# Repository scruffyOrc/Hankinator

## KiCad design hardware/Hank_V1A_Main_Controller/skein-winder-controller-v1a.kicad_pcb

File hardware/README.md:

# Hank hardware sources

This directory contains the editable KiCad sources and the corresponding
released manufacturing artifacts for the hardware used by Hank Winder V1.

| Directory | Board | Release source |
| --- | --- | --- |
| `Hank_V1A_Main_Controller` | Hank V1A main controller | V1A released controller package |
| `Load_Cell_System` | HX711 breakout and front/rear smart-foot load-cell boards | Load-cell-system release package |
| `Distribution_Block_v1.1` | Load-cell distribution block | v1.1 confirmed JLC release |
| `Hall_Effect_Board_A2` | Hall-effect sensor board | A2 release package |
| `Hank_Touchscreen_Adapter` | V1A-to-touchscreen adapter | Rev A two-layer package |

KiCad local state files (`*.kicad_prl`), lock files, and local `.history`
directories are intentionally excluded. They are machine-specific and are not
authoritative design data.

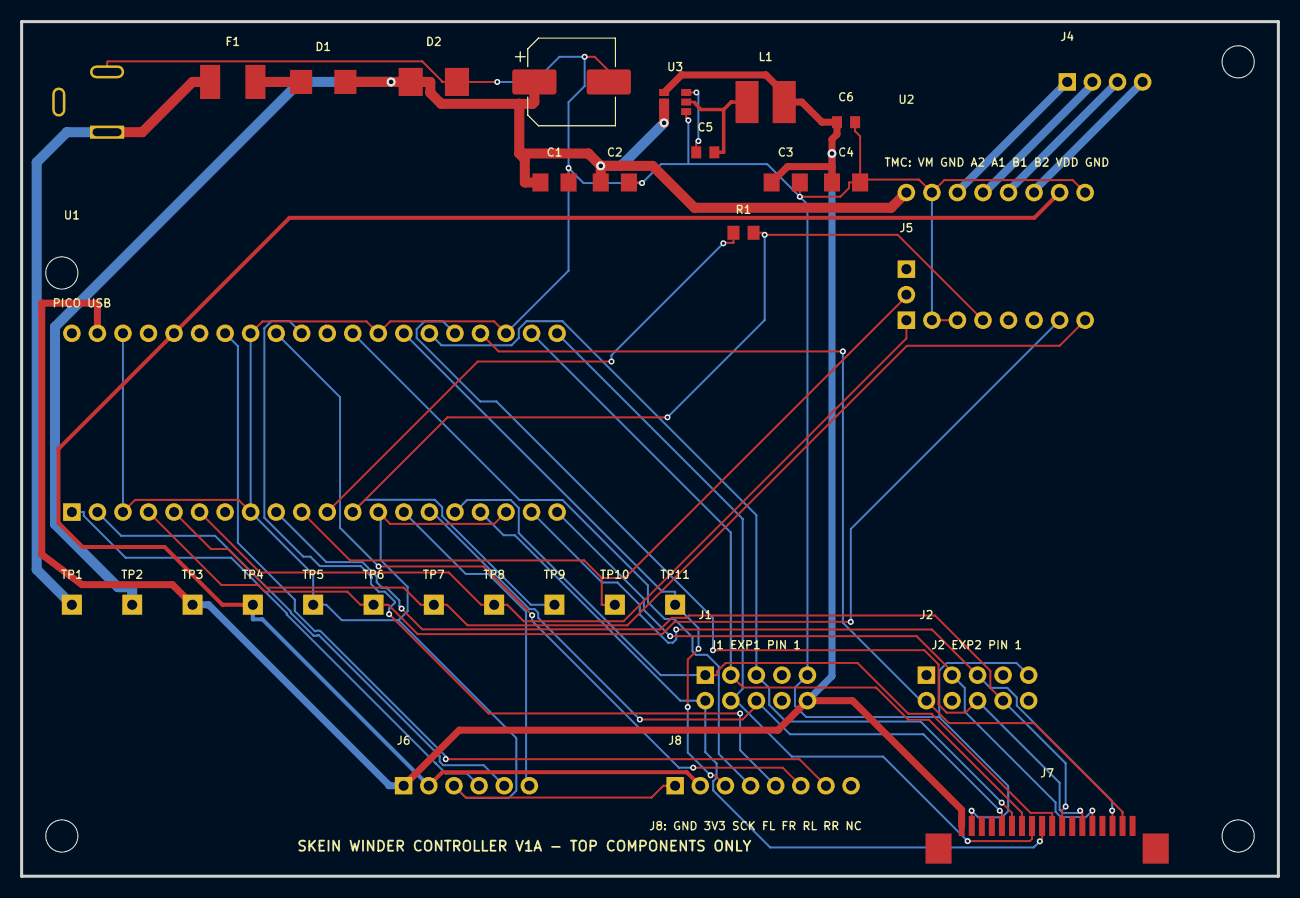
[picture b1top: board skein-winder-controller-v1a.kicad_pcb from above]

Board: 2 copper layers, 125.0 x 85.0 mm, 38 parts (0 on the bottom side), 37 nets.

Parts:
C1: 10uF 35V; C1
C2: 10uF 35V; C2
C3: 22uF 10V; C3
C4: 22uF 10V; C4
C5: 100nF bootstrap; C5
C6: 100nF 5V; C6
C7: CP_Elec_8x10.5
D1: SS54 series reverse-polarity diode; D1
D2: SMBJ18A TVS; D2
F1: PTC 1.1A 1812; F1
H1: M3 NPTH; H1
H2: M3 NPTH; H2
H3: M3 NPTH; H3
H4: M3 NPTH; H4
J1: Mini12864 J1 keyed 2x5 cable header; J1
J2: Mini12864 J2 keyed 2x5 cable header; J2
J3: Measured 5.5x2.1 center-positive blade DC jack; J3
J4: Motor A2 A1 B1 B2; J4
J5: BTT TMC2209 VREF/DIAG 1x2 female socket; J5
J6: Expansion 5V 3V3 GND GP0 GP1 GP10; J6
J7: Mini12864 V2 FPC AFA07-S18FCC-00 C23826; J7
J8: HX711 smart-foot harness GND 3V3 SCK FL FR RL RR 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; J8
L1: 4.7uH 3A; L1
R1: 1k TMC UART TX resistor 0805; R1
TP1: 12V_RAW test point; TP1
TP2: 12V_PROT test point; TP2
TP3: 5V test point; TP3
TP4: 3V3 test point; TP4
TP5: GND test point; TP5
TP6: STEP test point; TP6
TP7: DIR test point; TP7
TP8: EN test point; TP8
TP9: TMC_UART test point; TP9
TP10: TMC_DIAG test point; TP10
TP11: HX_SCK test point; TP11
U1: Raspberry Pi Pico-family 40-pin socket; USB LEFT; U1
U2: BTT TMC2209 V1.2 socket; U2
U3: AP63205WU-7 fixed 5V; U3

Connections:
3V3: J6.2, J8.2, TP4.1, U1.36, U2.15
5V: C3.1, C4.1, C6.1, J1.10, J6.1, J7.1, L1.2, TP3.1, U1.39, U3.1
12V_FUSED: D1.2, F1.2
12V_PROT: C1.1, C2.1, C7.1, D1.1, D2.1, TP2.1, U2.9, U3.2, U3.3
12V_RAW: F1.1, J3.1, TP1.1
A1: J4.2, U2.12
A2: J4.1, U2.11
B1: J4.3, U2.13
B2: J4.4, U2.14
BEEP: J1.1, J7.10, U1.16
BST: C5.1, U3.6
DIR: TP7.1, U1.5, U2.8
EN: TP8.1, U1.6, U2.1
ENC_A: J2.5, J7.16, U1.19
ENC_B: J2.3, J7.14, U1.20
ENC_BTN: J1.2, J7.9, U1.17
GND: C1.2, C2.2, C3.2, C4.2, C6.2, C7.2, D2.2, J1.9, J2.9, J3.2, J6.3, J7.2, J8.1, TP5.1, U1.3, U1.8, U1.13, U1.18, U1.23, U1.28, U1.33, U1.38, U2.2, U2.3, U2.10, U2.16, U3.4
GP0: J6.4, U1.1
GP1: J6.5, U1.2
GP10: J6.6, U1.14
HX_FL: J8.4, U1.29
HX_FR: J8.5, U1.31
HX_RL: J8.6, U1.32
HX_RR: J8.7, U1.34
HX_SCK: J8.3, TP11.1, U1.27
LCD_CLK: J2.2, J7.17, U1.24
LCD_CS: J1.3, J7.7, U1.22
LCD_MOSI: J2.6, J7.13, U1.25
LCD_RS: J1.4, J7.8, U1.21
LCD_RST: J1.5, J7.6, U1.26
RGB: J1.6, J7.5, U1.15
STEP: TP6.1, U1.4, U2.7
STOP: J2.8, J7.11, U1.9
SW: C5.2, L1.1, U3.5
TMC_DIAG: J5.2, TP10.1, U1.10
TMC_UART: R1.2, TP9.1, U1.12, U2.4
TMC_UART_TX: R1.1, U1.11

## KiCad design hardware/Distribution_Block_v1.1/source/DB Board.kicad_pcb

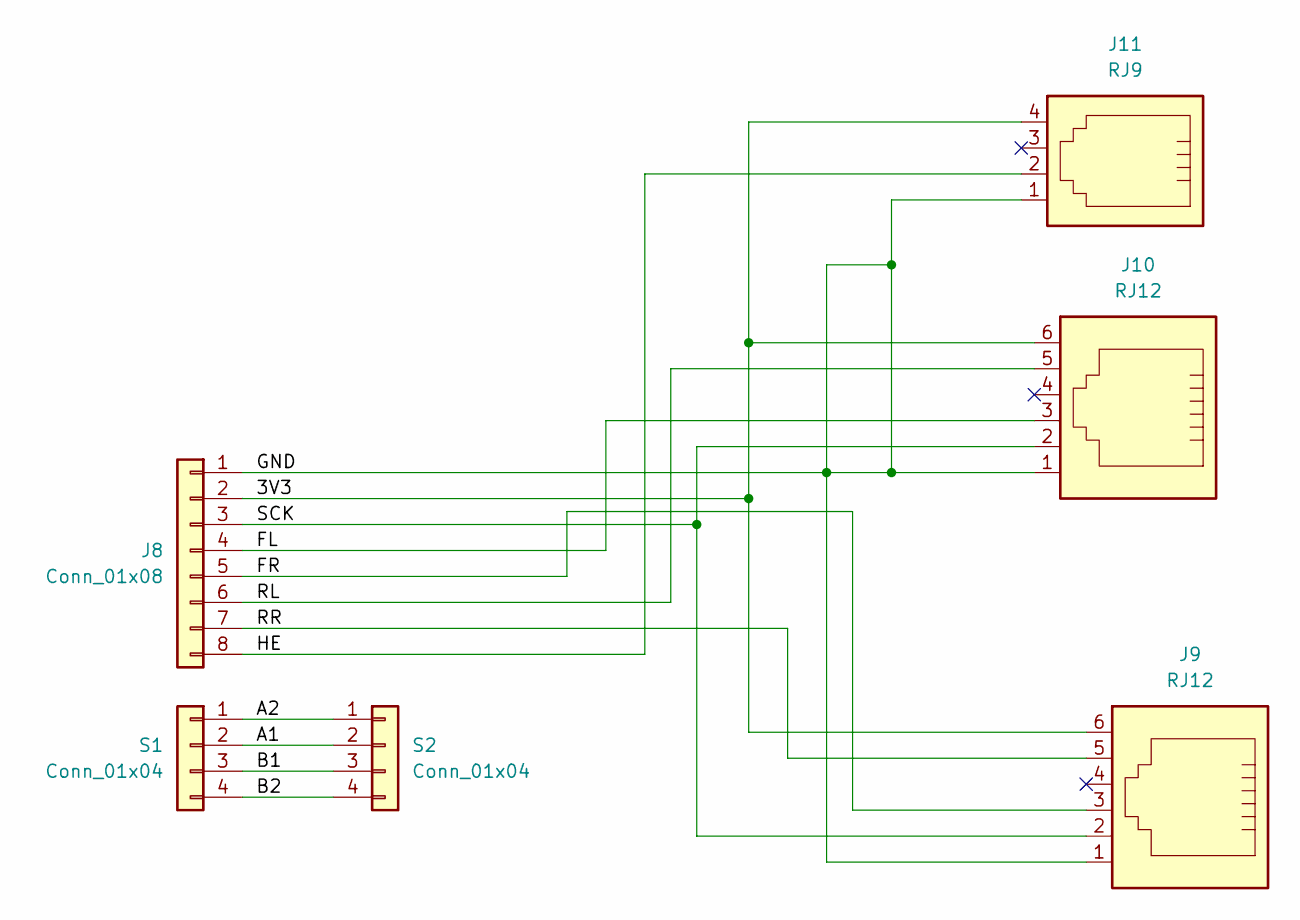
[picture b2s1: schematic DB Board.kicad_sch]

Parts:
J8: Conn_01x08; JST_XH_B8B-XH-A_1x08_P2.50mm_Vertical
J9, J10: RJ12; RJ25_Wayconn_MJEA-660X1_Horizontal
J11: RJ9; RJ9_Evercom_5501-4P4C-13MM_Horizontal
S1, S2: Conn_01x04; JST_XH_B4B-XH-A_1x04_P2.50mm_Vertical

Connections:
/3V3: J8.2, J9.6, J10.6, J11.4
/A1: S1.2, S2.2
/A2: S1.1, S2.1
/B1: S1.3, S2.3
/B2: S1.4, S2.4
/FL: J8.4, J10.3
/FR: J8.5, J9.3
/GND: J8.1, J9.1, J10.1, J11.1
/HE: J8.8, J11.2
/RL: J8.6, J10.5
/RR: J8.7, J9.5
/SCK: J8.3, J9.2, J10.2

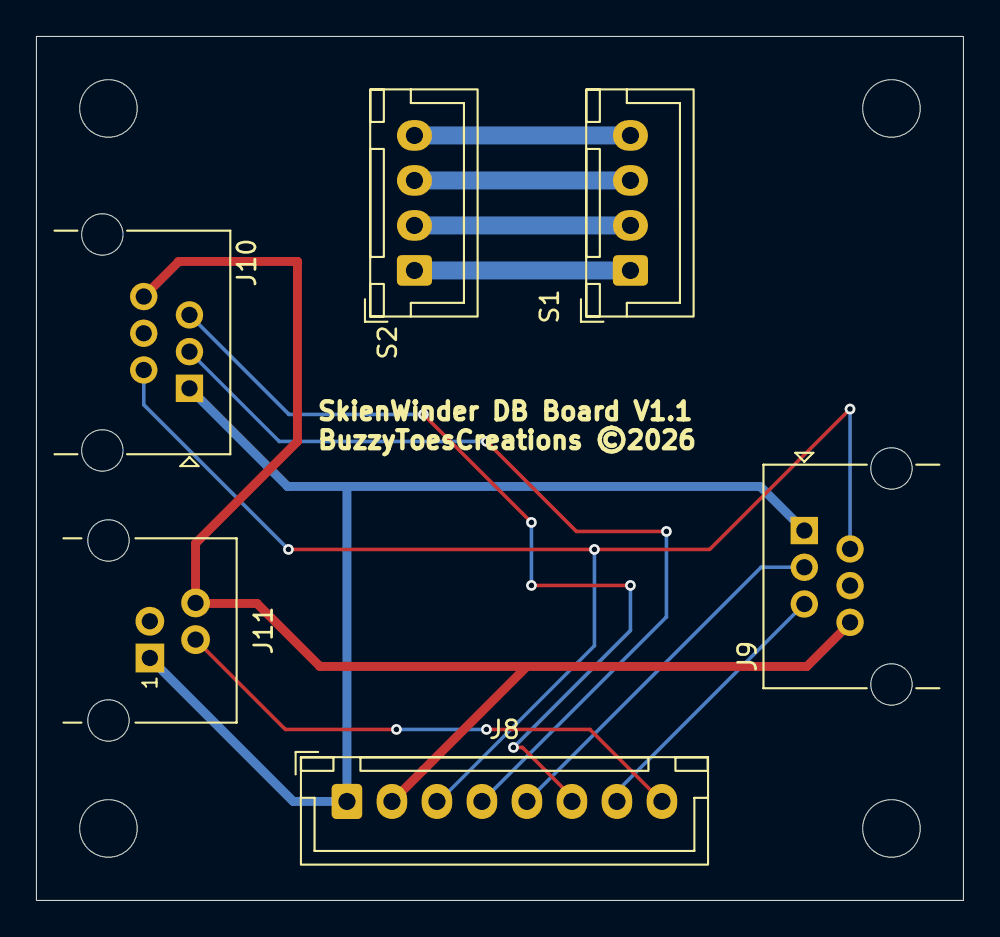
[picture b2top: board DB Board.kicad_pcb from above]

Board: 2 copper layers, 51.5 x 48.0 mm, 10 parts (0 on the bottom side), 12 nets.

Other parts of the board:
H1, H2, H3, H4: MountingHole_3.2mm_M3

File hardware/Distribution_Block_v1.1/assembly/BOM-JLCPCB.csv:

"Comment","Designator","Footprint","LCSC Part #"
"B8B-XH-A(LF)(SN)","J8","JST_XH_B8B-XH-A_1x08_P2.50mm_Vertical","C157972"
"B4B-XH-A(LF)(SN)","S1,S2","JST_XH_B4B-XH-A_1x04_P2.50mm_Vertical","C144395"
"R-RJ11R06P-A801","J9,J10","RJ25_Wayconn_MJEA-660X1_Horizontal","C189747"
"5501-4P4C-13MM","J11","RJ9_Evercom_5501-4P4C-13MM_Horizontal","C3097719"

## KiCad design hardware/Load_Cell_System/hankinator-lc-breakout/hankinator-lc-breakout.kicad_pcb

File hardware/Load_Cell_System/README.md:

# Hankinator load-cell breakout A0

Start with [APPROVAL.html](APPROVAL.html) or [APPROVAL.md](APPROVAL.md). Three editable KiCad 10 projects, preliminary placement only. No Gerbers. See approval report for unresolved sourcing and physical verification gates.

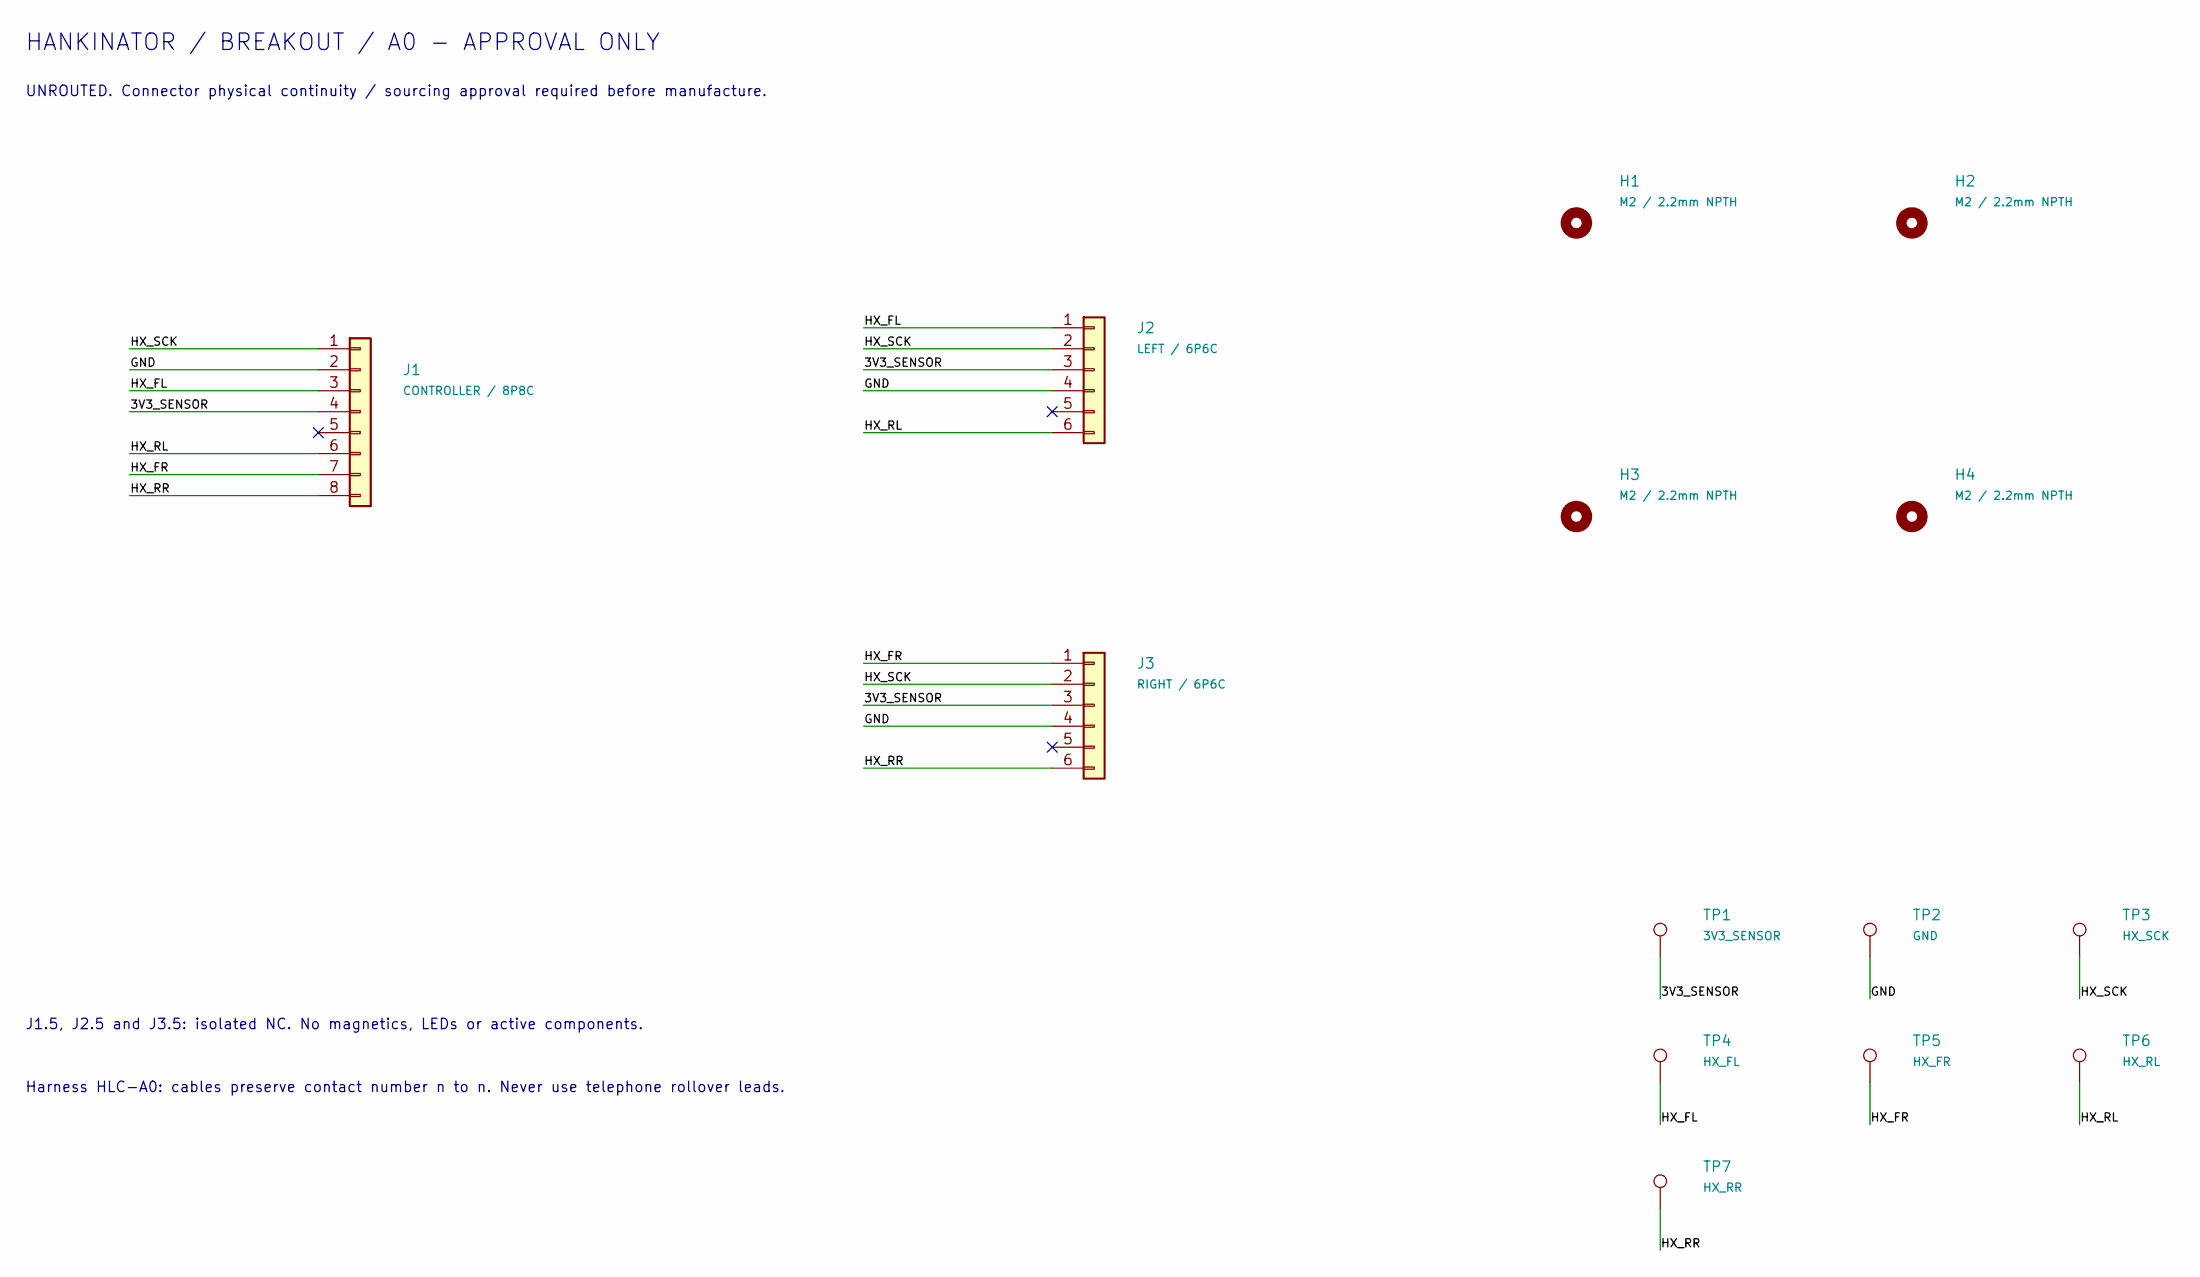
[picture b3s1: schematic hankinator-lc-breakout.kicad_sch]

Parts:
H1, H2, H3, H4: M2 / 2.2mm NPTH; MountingHole_2.2mm_M2
J1: CONTROLLER / 8P8C; WE_615008144221; MPN 615008144221
J2: LEFT / 6P6C; WE_615006143621; MPN 615006143621
J3: RIGHT / 6P6C; WE_615006143621; MPN 615006143621
TP1: 3V3_SENSOR; TestPoint_Pad_D1.5mm
TP2: GND; TestPoint_Pad_D1.5mm
TP3: HX_SCK; TestPoint_Pad_D1.5mm
TP4: HX_FL; TestPoint_Pad_D1.5mm
TP5: HX_FR; TestPoint_Pad_D1.5mm
TP6: HX_RL; TestPoint_Pad_D1.5mm
TP7: HX_RR; TestPoint_Pad_D1.5mm

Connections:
3V3_SENSOR: J1.4, J2.3, J3.3, TP1.1
GND: J1.2, J2.4, J3.4, TP2.1
HX_FL: J1.3, J2.1, TP4.1
HX_FR: J1.7, J3.1, TP5.1
HX_RL: J1.6, J2.6, TP6.1
HX_RR: J1.8, J3.6, TP7.1
HX_SCK: J1.1, J2.2, J3.2, TP3.1

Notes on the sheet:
HANKINATOR / BREAKOUT / A0 - APPROVAL ONLY
UNROUTED. Connector physical continuity / sourcing approval required before manufacture.
J1.5, J2.5 and J3.5: isolated NC. No magnetics, LEDs or active components.
Harness HLC-A0: cables preserve contact number n to n. Never use telephone rollover leads.

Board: 2 copper layers, 14 parts (0 on the bottom side), 7 nets, no tracks yet.

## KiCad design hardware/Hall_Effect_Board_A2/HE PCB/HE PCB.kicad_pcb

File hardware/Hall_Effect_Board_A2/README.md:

# Hankinator HE PCB A2

37 x 20 mm, two copper layers, nominal 1.6 mm FR4 / 1 oz copper. Separate project; DH/RL/FL and controller projects are unchanged.

## A2 changes

Removed 5 mm from the left end. The jack mouth is at CAD X=1, giving approximately 4 mm overhang past the new X=5 board edge. Both 2.3 mm locating holes remain intact; minimum laminate from each hole rim to the left edge is 0.85 mm. Connector mating clearance still needs housing review.

Corrected the sensor footprint from manufacturer bottom view to component-side view, rotated U1 by 180 degrees, and rerouted its supply/output pins. The required flat sensing face points RIGHT. A1's asserted orientation was incorrect; use the A2 Gerbers and CPL together. See POLARITY-REVIEW.md for the complete sensor, LED, MOSFET, and connector review and the required JLC preview orientation.

Added back-side silkscreen: ©Buzzytoes Creations 2026.

## Function

U1 is TI DRV5033AJQLPGM, JLCPCB C201608. Rated 2.5-38 V by the TI datasheet and used here at 3.3 V. It is a continuous digital omnipolar switch, not an analog sensor or a latching switch. Either pole can trigger it. AJ nominal switching thresholds are 6.9 mT operate / 3.5 mT release, with worst-case operate up to 12 mT. Do not assume the same trigger gap as the existing unidentified 3144E module.

D1 PWR and D2 TRIG are red 0603 SMD LEDs, individually labeled. D1 lights with supply. D2 lights while the magnet is detected and goes out when it leaves. It has no pulse stretcher: short detections can be hard to see, and a stationary magnet holds it on.

U1 pulls HALL_N low when detected. R1 is a local 4.7k pull-up to 3.3 V; R2 is 100 ohms in series with the HE cable signal. AO3401A Q1 switches the trigger LED supply, so its LED current does not flow in the sensor output or HE wire. Q1 does add gate capacitance; firmware should measure actual pulse timing if required. C1 is 100 nF near U1; C2 is 10 uF at the input. Each LED has a 1k current-limiting resistor.

## Connector and cable

J1 is the same EVERCOM 5501-4P4C-13MM / C3097719 jack as DH J11. It opens out of the left end. Use a cable verified contact n to contact n; telephone handset cables may reverse contacts.

| Jack contact | DH J11 | Hall J1 |
|---|---|---|
| 1 | GND | GND |
| 2 | HE | HE, active low |
| 3 | Unused | No connect |
| 4 | 3V3 | 3V3_SENSOR |

This is the HALL port mapping, not the smart-foot 4P4C mapping. Connect only to DH J11. The controller Hall allocation remains GP10; verify the installed controller harness actually routes HE there. No firmware or main controller change is included.

## Physical pin check

Component-side PCB coordinates in mm, retaining the A1 CAD origin, X right and Y down. The new outline spans X=5 to 42 and Y=0 to 20; subtract 5 from X to measure from the new left edge:

| J1 contact | X | Y | Function |
|---|---:|---:|---|
| 1, square pad | 9.30 | 11.53 | GND |
| 2 | 11.84 | 10.51 | HE |
| 3 | 9.30 | 9.49 | NC |
| 4 | 11.84 | 8.47 | 3.3 V |

Jack pegs are at (7,5) and (7,15), 2.3 mm NPTH. Signal holes are 0.9 mm. These numbered pad offsets and the 270-degree jack orientation were compared directly against DH J11 and match exactly. The selected manufacturer drawing is included. Do not interpret the staggered solder tails as the plug contact order or mirror this component-side table for fabrication. On the solder side the visual order is reversed. Verify plug contact continuity to the square GND pad and each numbered pad before applying power.

U1 has 1.27 mm pitch and TI's recommended 1.07 x 1.70 mm pads / 0.75 mm drill, from drawing 4221343/C. Pins are 1 VCC, 2 GND, 3 OUT. On this PCB, their coordinates are (40,8.73), (40,10), (40,11.27). The upright flat sensing face points toward the right board edge, as marked MAGNET >. The face is approximately 1.46 mm inside the board edge. Present the magnet toward that face, parallel to the board plane. Mounting height, magnet gap and housing clearance require a prototype check; there is no verified detection-distance claim.

Two 3.2 mm M3 NPTH mounting holes are centered at (18.5,3.5) and (18.5,16.5), 13 mm apart. Use nonmagnetic hardware around the Hall sensor. Leave jack latch and plug withdrawal clearance. The jack is approximately 14.5 mm tall; housing geometry has not been verified.

## Current and traces

All traces are at least 0.20 mm; the short bottom HE connection is 0.25 mm. B.Cu has a continuous ground reference around the short signal route. At 3.3 V, each red LED is approximately 0.9-1.5 mA using the listed 1.8-2.4 V forward range; brightness at these currents must be checked. U1 is 2.7 mA typical, 3.6 mA maximum at 125 C. The active pull-up draws approximately 0.70 mA. The combined conservative operating budget is below 10 mA, excluding external loads on HE.

For a conservative 50 mm long, 0.20 mm wide, 35 um copper trace, resistance is approximately 0.123 ohm at 20 C. At 10 mA this is 1.23 mV drop and 12.3 uW dissipation. These trace widths comfortably support the board's current. Supply drop in the external harness and magnetic switching behavior remain separate checks.

## Files and validation

- `HE PCB/`: editable KiCad schematic, PCB and project; project-local libraries in `libraries/`.
- `HE-PCB-Gerbers.zip`: fabrication layers and separate PTH/NPTH drills.
- `assembly/BOM-JLCPCB.csv` and `assembly/CPL-JLCPCB.csv`: 11 populated components; mounting holes and bare test pads excluded.
- `checks/`: native ERC, native DRC with schematic parity, XML netlist, connector/pad-net audit and assembly inspections.
- `DRILL-COORDINATE-AUDIT.txt`: every exported drill coordinate compared against the PCB.
- `review/`: schematic and board views. Bottom view is shown through the board from the component side, so lettering appears mirrored.

KiCad 10.0.5: ERC 0 errors / 0 warnings; DRC 0 violations / 0 unconnected pads / 0 schematic parity issues under saved project rules. Default ignored check categories are listed in the reports; no individual violations were excluded. CAD checks do not establish physical jack fit, cable continuity, magnet gap, or assembled operation.

## JLCPCB quote / assembly

Upload the Gerber ZIP as a new board item with the BOM and CPL. CPL uses the NEW lower-left board origin at CAD (5,20), millimeters, X right and Y up. Its X coordinates are 5 mm smaller than A1. J1 and U1 coordinates are corrected to their body centers; native KiCad anchor positions are retained in checks/native-positions.csv for comparison. Verify JLC's placement preview: J1 mouth left, U1 flat face right, LED cathodes/pin 1 left. J1 and U1 require through-hole assembly; small-board panel/fixture requirements and costs are determined by JLC.

C201608 has a live JLC listing for wave-solder assembly, but a reliable current stock count was not exposed on the retrieved page. Recheck availability during quoting; do not substitute an unspecified 3144E. Other BOM stock has not been freshly counted for this package. No order has been placed. These files support quoting and first-article fabrication; assembly orientation and actual cable/magnet checks remain required before production use.

## Sources

- TI DRV5033 datasheet: https://www.ti.com/lit/ds/symlink/drv5033.pdf
- JLC sensor listing: https://jlcpcb.com/partdetail/TexasInstruments-DRV5033AJQLPGM/C201608
- AO3401A manufacturer datasheet: https://www.aosmd.com/sites/default/files/res/datasheets/AO3401A.pdf
- JLC Q1 listing: https://jlcpcb.com/partdetail/Alpha_OmegaSemicon-AO3401A/C15127
- JLC LED listing: https://jlcpcb.com/partdetail/Hubei_KentoElec-KT0603R/C2286
- EVERCOM drawing: https://atta.szlcsc.com/upload/public/pdf/source/20220705/442A4794DE2D8659C3975B8A2EE8C1A4.pdf

Prepared 2026-09-30.

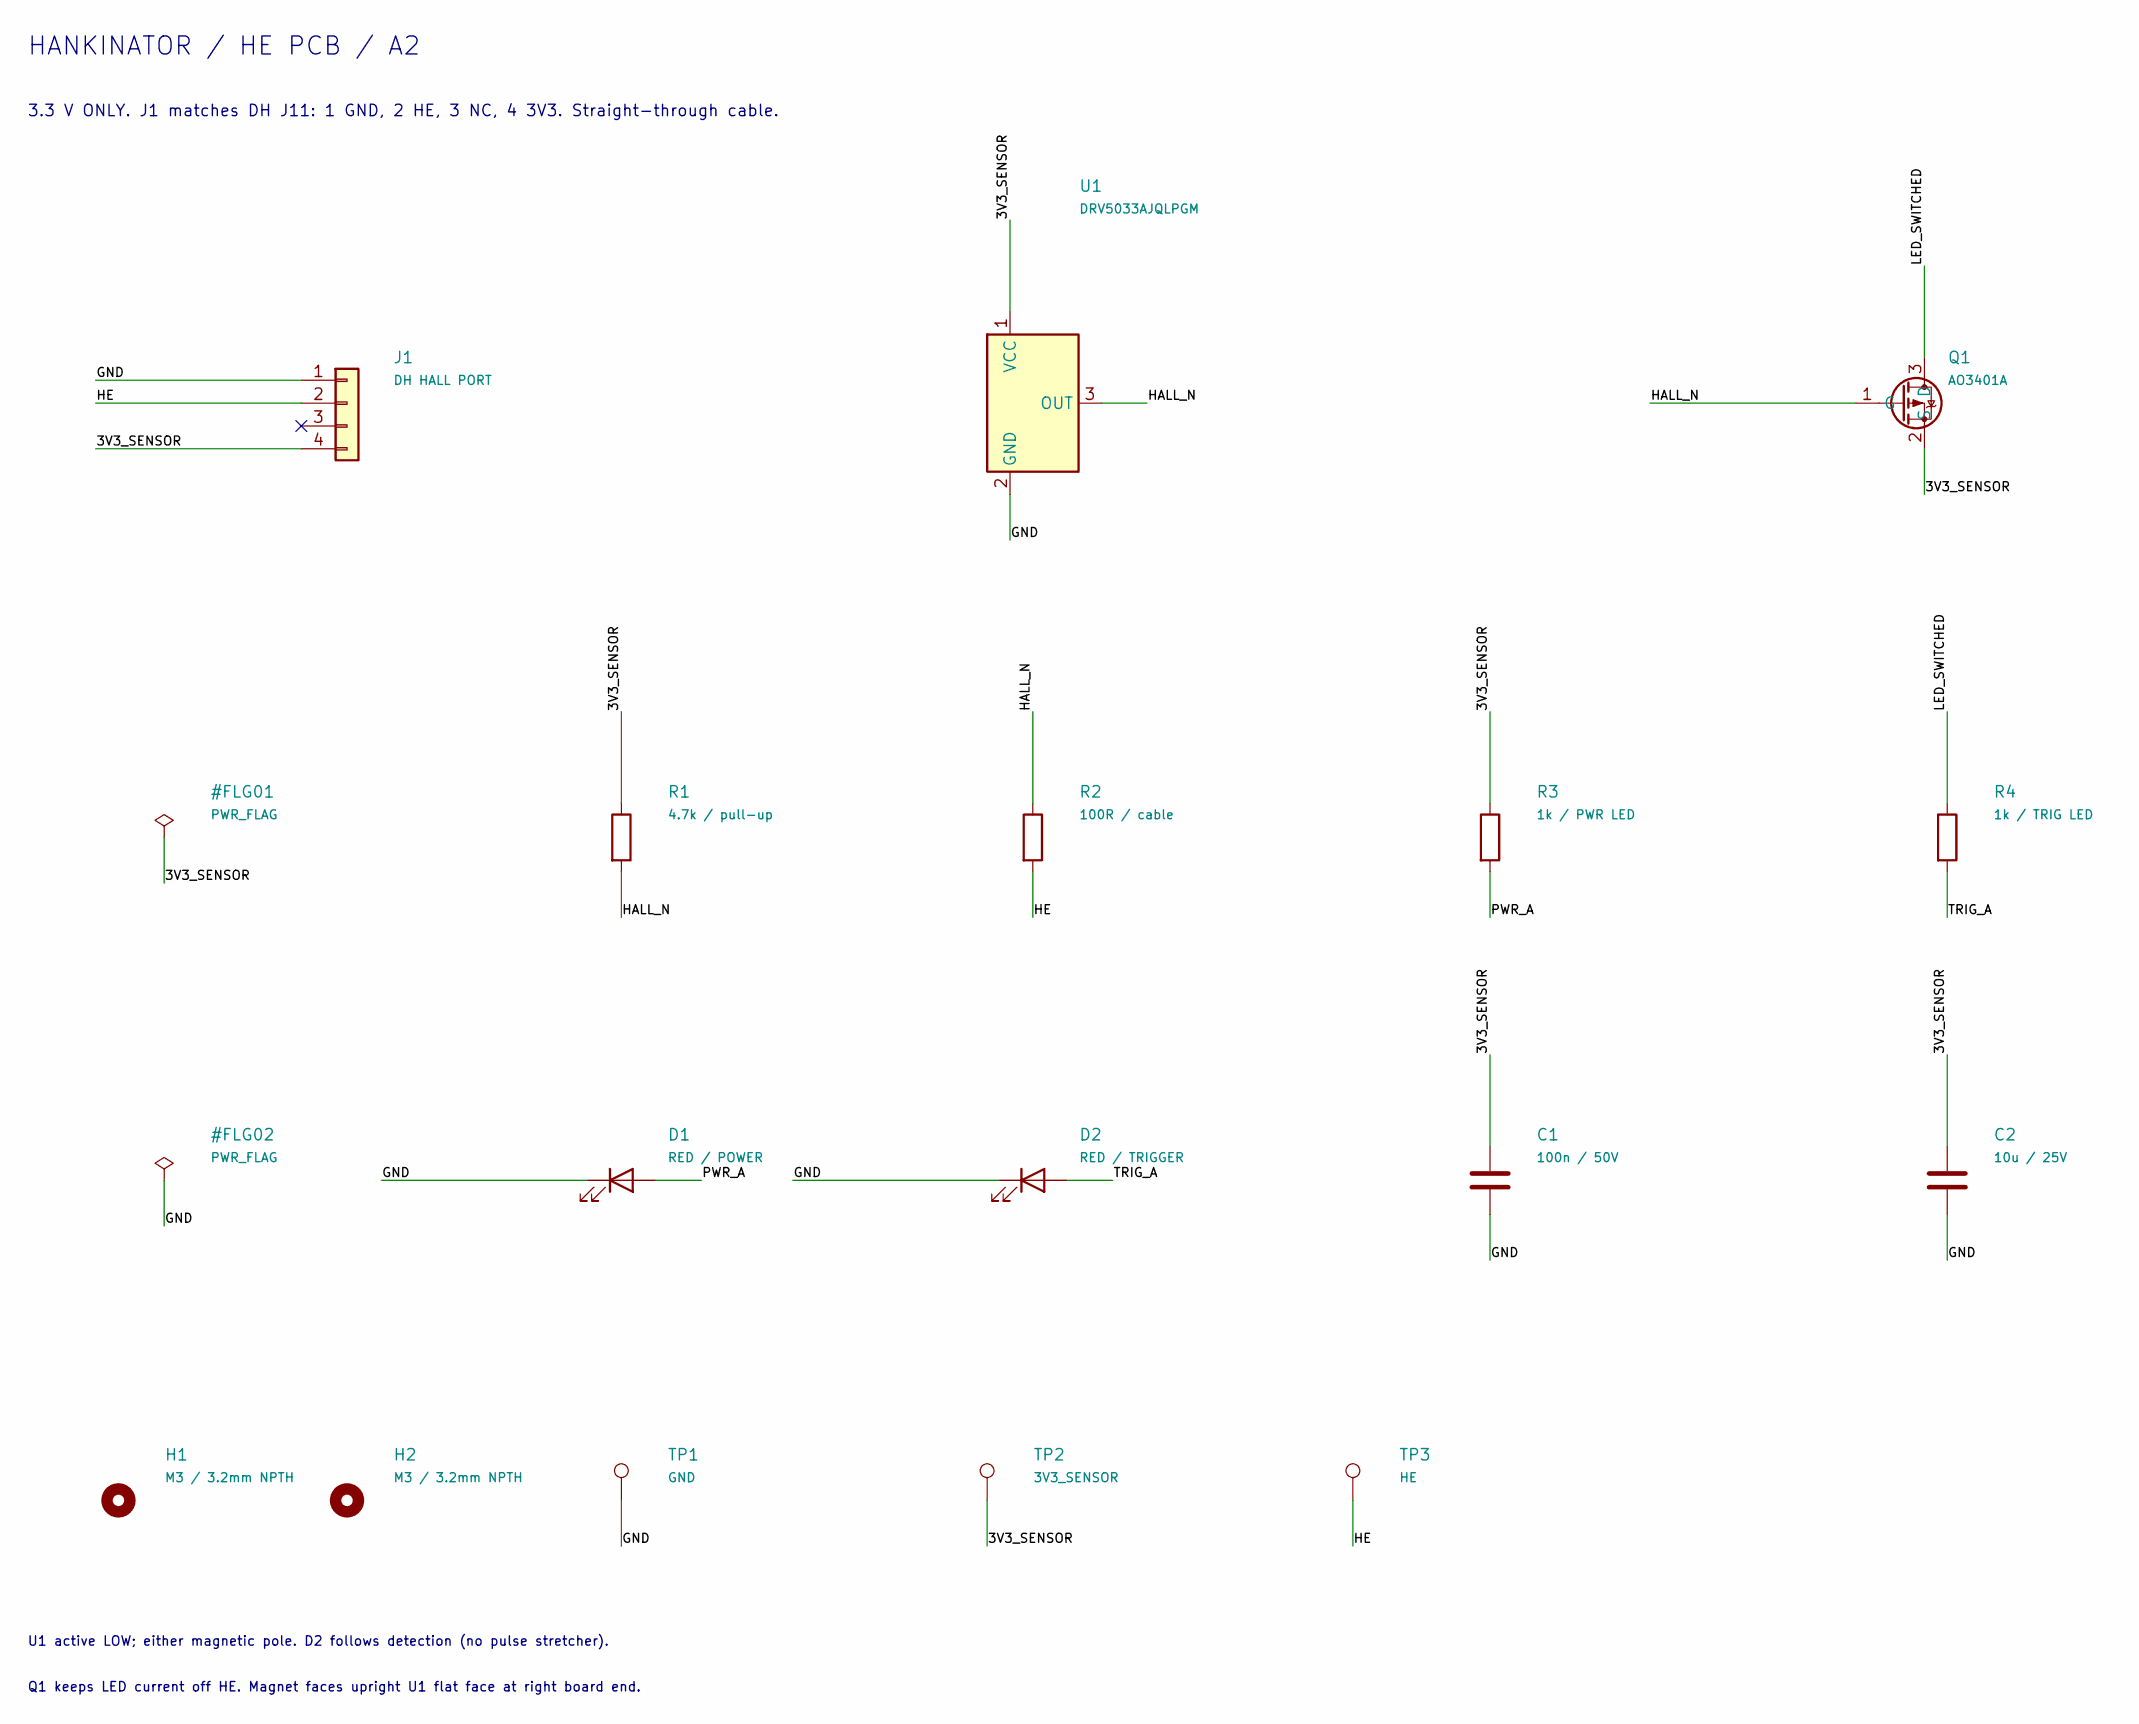
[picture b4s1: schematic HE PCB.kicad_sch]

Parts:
C1: 100n / 50V; C_0603_1608Metric; MPN CL10B104KB8NNNC; LCSC C1591
C2: 10u / 25V; C_0805_2012Metric; MPN CL21A106KAYNNNE; LCSC C15850
D1: RED / POWER; LED_0603_1608Metric; MPN KT-0603R; LCSC C2286
D2: RED / TRIGGER; LED_0603_1608Metric; MPN KT-0603R; LCSC C2286
H1, H2: M3 / 3.2mm NPTH; MountingHole_3.2mm_M3
J1: DH HALL PORT; Evercom_5501-4P4C-13MM; MPN 5501-4P4C-13MM; LCSC C3097719
Q1: AO3401A; SOT-23; MPN AO3401A; LCSC C15127
R1: 4.7k / pull-up; R_0603_1608Metric; MPN 0603WAF4701T5E; LCSC C23162
R2: 100R / cable; R_0603_1608Metric; MPN 0603WAF1000T5E; LCSC C22775
R3: 1k / PWR LED; R_0603_1608Metric; MPN 0603WAF1001T5E; LCSC C21190
R4: 1k / TRIG LED; R_0603_1608Metric; MPN 0603WAF1001T5E; LCSC C21190
TP1: GND; TestPoint_Pad_D1.5mm
TP2: 3V3_SENSOR; TestPoint_Pad_D1.5mm
TP3: HE; TestPoint_Pad_D1.5mm
U1: DRV5033AJQLPGM; TI_LPG0003A; MPN DRV5033AJQLPGM; LCSC C201608

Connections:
/3V3_SENSOR: C1.1, C2.1, J1.4, Q1.2 (S), R1.1, R3.1, TP2.1, U1.1 (VCC)
/GND: C1.2, C2.2, D1.1 (K), D2.1 (K), J1.1, TP1.1, U1.2 (GND)
/HALL_N: Q1.1 (G), R1.2, R2.1, U1.3 (OUT)
/HE: J1.2, R2.2, TP3.1
/LED_SWITCHED: Q1.3 (D), R4.1
/PWR_A: D1.2 (A), R3.2
/TRIG_A: D2.2 (A), R4.2

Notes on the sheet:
HANKINATOR / HE PCB / A2
3.3 V ONLY. J1 matches DH J11: 1 GND, 2 HE, 3 NC, 4 3V3. Straight-through cable.
U1 active LOW; either magnetic pole. D2 follows detection (no pulse stretcher).
Q1 keeps LED current off HE. Magnet faces upright U1 flat face at right board end.

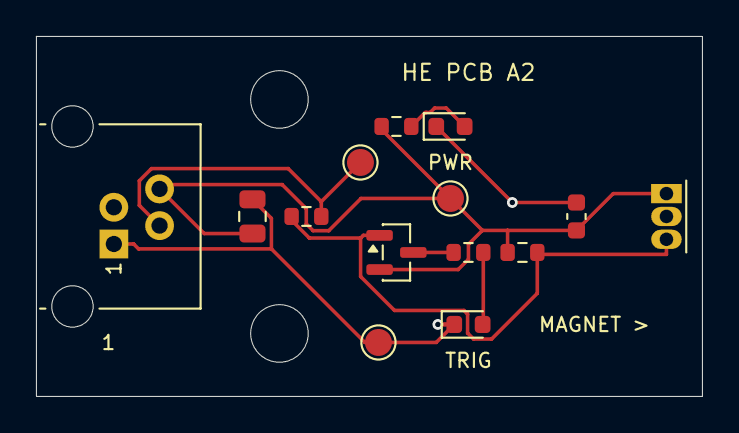
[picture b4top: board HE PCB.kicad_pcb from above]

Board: 2 copper layers, 37.0 x 20.0 mm, 16 parts (0 on the bottom side), 7 nets.

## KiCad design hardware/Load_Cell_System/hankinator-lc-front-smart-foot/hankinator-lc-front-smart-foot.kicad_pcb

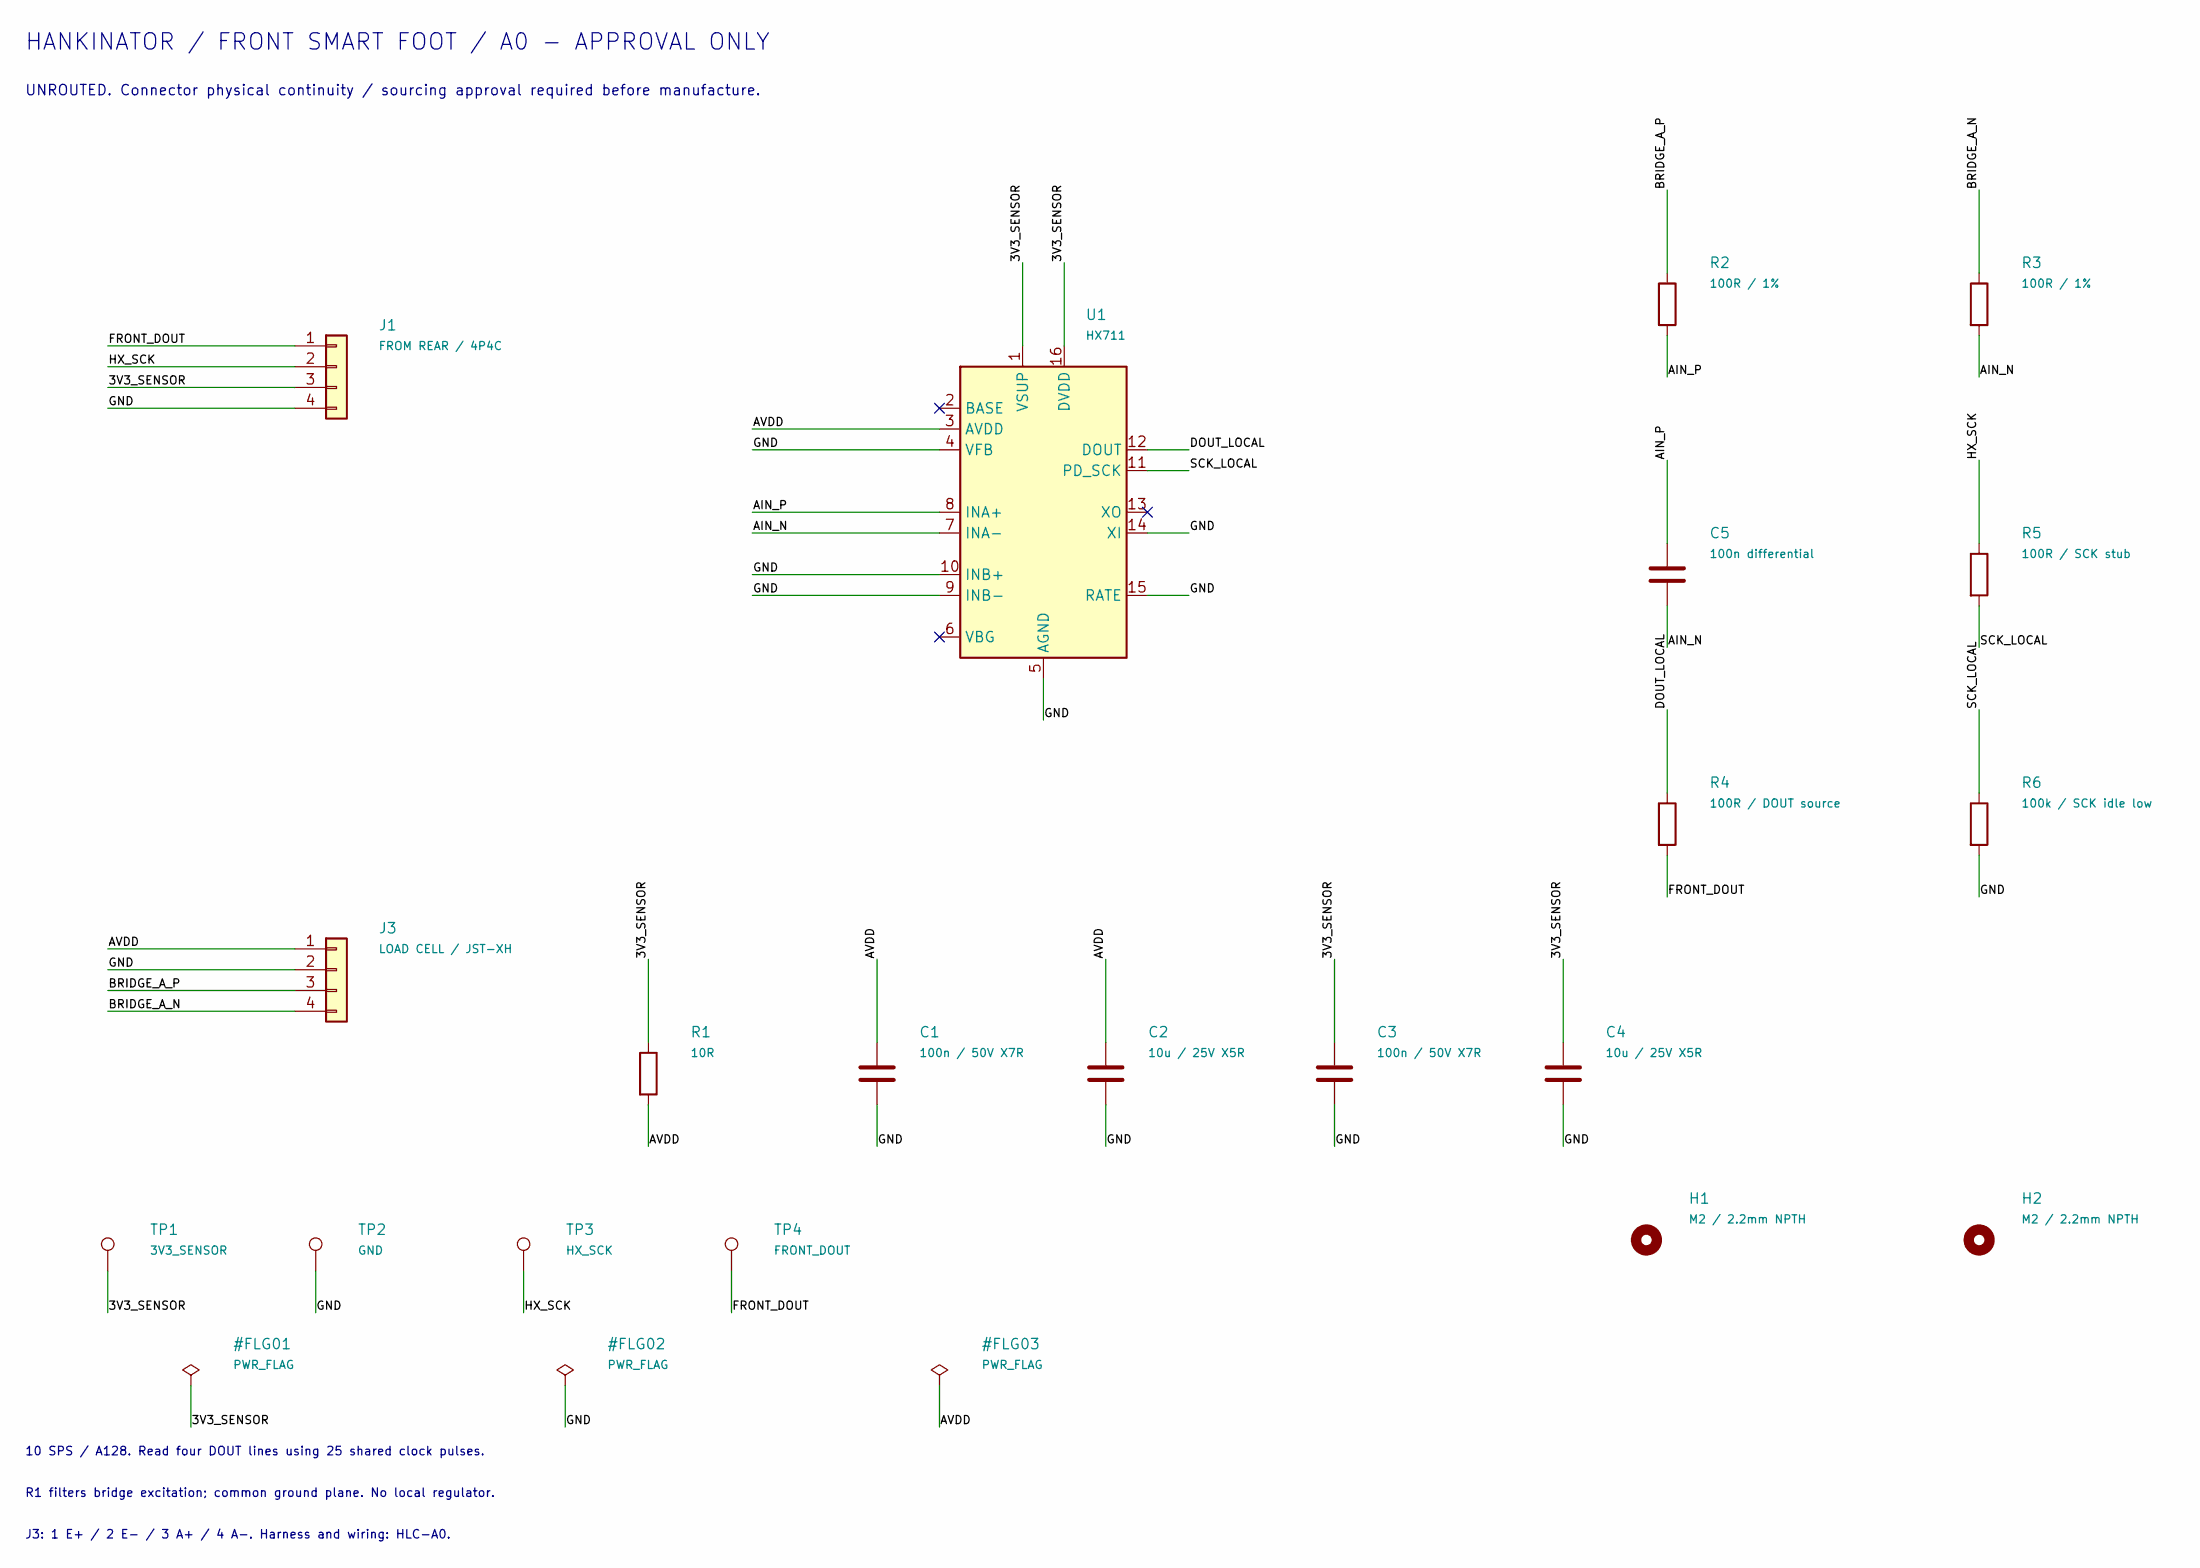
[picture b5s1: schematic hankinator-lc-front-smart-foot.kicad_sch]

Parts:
C1, C3: 100n / 50V X7R; C_0603_1608Metric; MPN CL10B104KB8NNNC; LCSC C1591
C2, C4: 10u / 25V X5R; C_0805_2012Metric; MPN CL21A106KAYNNNE; LCSC C15850
C5: 100n differential; C_0603_1608Metric; MPN CL10B104KB8NNNC; LCSC C1591
H1, H2: M2 / 2.2mm NPTH; MountingHole_2.2mm_M2
J1: FROM REAR / 4P4C; WE_615004143821; MPN 615004143821
J3: LOAD CELL / JST-XH; JST_XH_B4B-XH-A_1x04_P2.50mm_Vertical; MPN B4B-XH-A(LF)(SN); LCSC C144395
R1: 10R; R_0603_1608Metric; MPN 0603WAF100JT5E; LCSC C22859
R2, R3: 100R / 1%; R_0603_1608Metric; MPN 0603WAF1000T5E; LCSC C22775
R4: 100R / DOUT source; R_0603_1608Metric; MPN 0603WAF1000T5E; LCSC C22775
R5: 100R / SCK stub; R_0603_1608Metric; MPN 0603WAF1000T5E; LCSC C22775
R6: 100k / SCK idle low; R_0603_1608Metric; MPN 0603WAF1003T5E; LCSC C25803
TP1: 3V3_SENSOR; TestPoint_Pad_D1.5mm
TP2: GND; TestPoint_Pad_D1.5mm
TP3: HX_SCK; TestPoint_Pad_D1.5mm
TP4: FRONT_DOUT; TestPoint_Pad_D1.5mm
U1: HX711; SOIC-16_3.9x9.9mm_P1.27mm; MPN HX711; LCSC C43656

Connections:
3V3_SENSOR: C3.1, C4.1, J1.3, R1.1, TP1.1, U1.1 (VSUP), U1.16 (DVDD)
AIN_N: C5.2, R3.2, U1.7 (INA-)
AIN_P: C5.1, R2.2, U1.8 (INA+)
AVDD: C1.1, C2.1, J3.1, R1.2, U1.3 (AVDD)
BRIDGE_A_N: J3.4, R3.1
BRIDGE_A_P: J3.3, R2.1
DOUT_LOCAL: R4.1, U1.12 (DOUT)
FRONT_DOUT: J1.1, R4.2, TP4.1
GND: C1.2, C2.2, C3.2, C4.2, J1.4, J3.2, R6.2, TP2.1, U1.4 (VFB), U1.5 (AGND), U1.9 (INB-), U1.10 (INB+), U1.14 (XI), U1.15 (RATE)
HX_SCK: J1.2, R5.1, TP3.1
SCK_LOCAL: R5.2, R6.1, U1.11 (PD_SCK)

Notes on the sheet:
HANKINATOR / FRONT SMART FOOT / A0 - APPROVAL ONLY
UNROUTED. Connector physical continuity / sourcing approval required before manufacture.
10 SPS / A128. Read four DOUT lines using 25 shared clock pulses.
R1 filters bridge excitation; common ground plane. No local regulator.
J3: 1 E+ / 2 E- / 3 A+ / 4 A-. Harness and wiring: HLC-A0.

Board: 2 copper layers, 20 parts (0 on the bottom side), 11 nets, no tracks yet.

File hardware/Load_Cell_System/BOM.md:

# Approval BOM

Per-design quantities below. System quantity is one breakout, two rear and two front boards. Mounting holes/test points are PCB features, not purchased components. Selected modular-jack assembly sourcing remains unresolved; see APPROVAL.md. Passive stock and assembly availability must be refreshed at order time.

## hankinator-lc-breakout

| Reference | Value | Manufacturer | MPN | LCSC |
|---|---|---|---|---|
|J1|CONTROLLER / 8P8C|Wurth Elektronik|615008144221|Unverified|
|J2|LEFT / 6P6C|Wurth Elektronik|615006143621|Unverified|
|J3|RIGHT / 6P6C|Wurth Elektronik|615006143621|Unverified|

## hankinator-lc-rear-smart-foot

| Reference | Value | Manufacturer | MPN | LCSC |
|---|---|---|---|---|
|J1|FROM BREAKOUT / 6P6C|Wurth Elektronik|615006143621|Unverified|
|J2|TO FRONT / 4P4C|Wurth Elektronik|615004143821|Unverified|
|J3|LOAD CELL / JST-XH|JST|B4B-XH-A(LF)(SN)|C144395|
|U1|HX711|Avia Semicon (Xiamen)|HX711|C43656|
|R1|10R|UNI-ROYAL|0603WAF100JT5E|C22859|
|C1|100n / 50V X7R|Samsung|CL10B104KB8NNNC|C1591|
|C2|10u / 25V X5R|Samsung|CL21A106KAYNNNE|C15850|
|C3|100n / 50V X7R|Samsung|CL10B104KB8NNNC|C1591|
|C4|10u / 25V X5R|Samsung|CL21A106KAYNNNE|C15850|
|R2|100R / 1%|UNI-ROYAL|0603WAF1000T5E|C22775|
|R3|100R / 1%|UNI-ROYAL|0603WAF1000T5E|C22775|
|C5|100n differential|Samsung|CL10B104KB8NNNC|C1591|
|R4|100R / DOUT source|UNI-ROYAL|0603WAF1000T5E|C22775|
|R5|100R / SCK stub|UNI-ROYAL|0603WAF1000T5E|C22775|
|R6|100k / SCK idle low|UNI-ROYAL|0603WAF1003T5E|C25803|

## hankinator-lc-front-smart-foot

| Reference | Value | Manufacturer | MPN | LCSC |
|---|---|---|---|---|
|J1|FROM REAR / 4P4C|Wurth Elektronik|615004143821|Unverified|
|J3|LOAD CELL / JST-XH|JST|B4B-XH-A(LF)(SN)|C144395|
|U1|HX711|Avia Semicon (Xiamen)|HX711|C43656|
|R1|10R|UNI-ROYAL|0603WAF100JT5E|C22859|
|C1|100n / 50V X7R|Samsung|CL10B104KB8NNNC|C1591|
|C2|10u / 25V X5R|Samsung|CL21A106KAYNNNE|C15850|
|C3|100n / 50V X7R|Samsung|CL10B104KB8NNNC|C1591|
|C4|10u / 25V X5R|Samsung|CL21A106KAYNNNE|C15850|
|R2|100R / 1%|UNI-ROYAL|0603WAF1000T5E|C22775|
|R3|100R / 1%|UNI-ROYAL|0603WAF1000T5E|C22775|
|C5|100n differential|Samsung|CL10B104KB8NNNC|C1591|
|R4|100R / DOUT source|UNI-ROYAL|0603WAF1000T5E|C22775|
|R5|100R / SCK stub|UNI-ROYAL|0603WAF1000T5E|C22775|
|R6|100k / SCK idle low|UNI-ROYAL|0603WAF1003T5E|C25803|

C1591: Samsung CL10B104KB8NNNC, 100 nF/50 V X7R 0603, [observed LCSC stock 2,115,600](https://www.lcsc.com/product-detail/C1591.html). C15850: CL21A106KAYNNNE, 10 uF/25 V X5R 0805, [JLC basic SMT listing](https://jlcpcb.com/partdetail/C15850); stock not verified. Resistors: [C22859 10 ohm](https://www.lcsc.com/product-detail/C22859.html), [C22775 100 ohm](https://jlcpcb.com/partdetail/C22775), [C25803 100 kohm](https://jlcpcb.com/partdetail/C25803); stock not verified.

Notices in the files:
hardware/Distribution_Block_v1.1/source/DB Board.kicad_pcb:
BuzzyToesCreations ©2026
